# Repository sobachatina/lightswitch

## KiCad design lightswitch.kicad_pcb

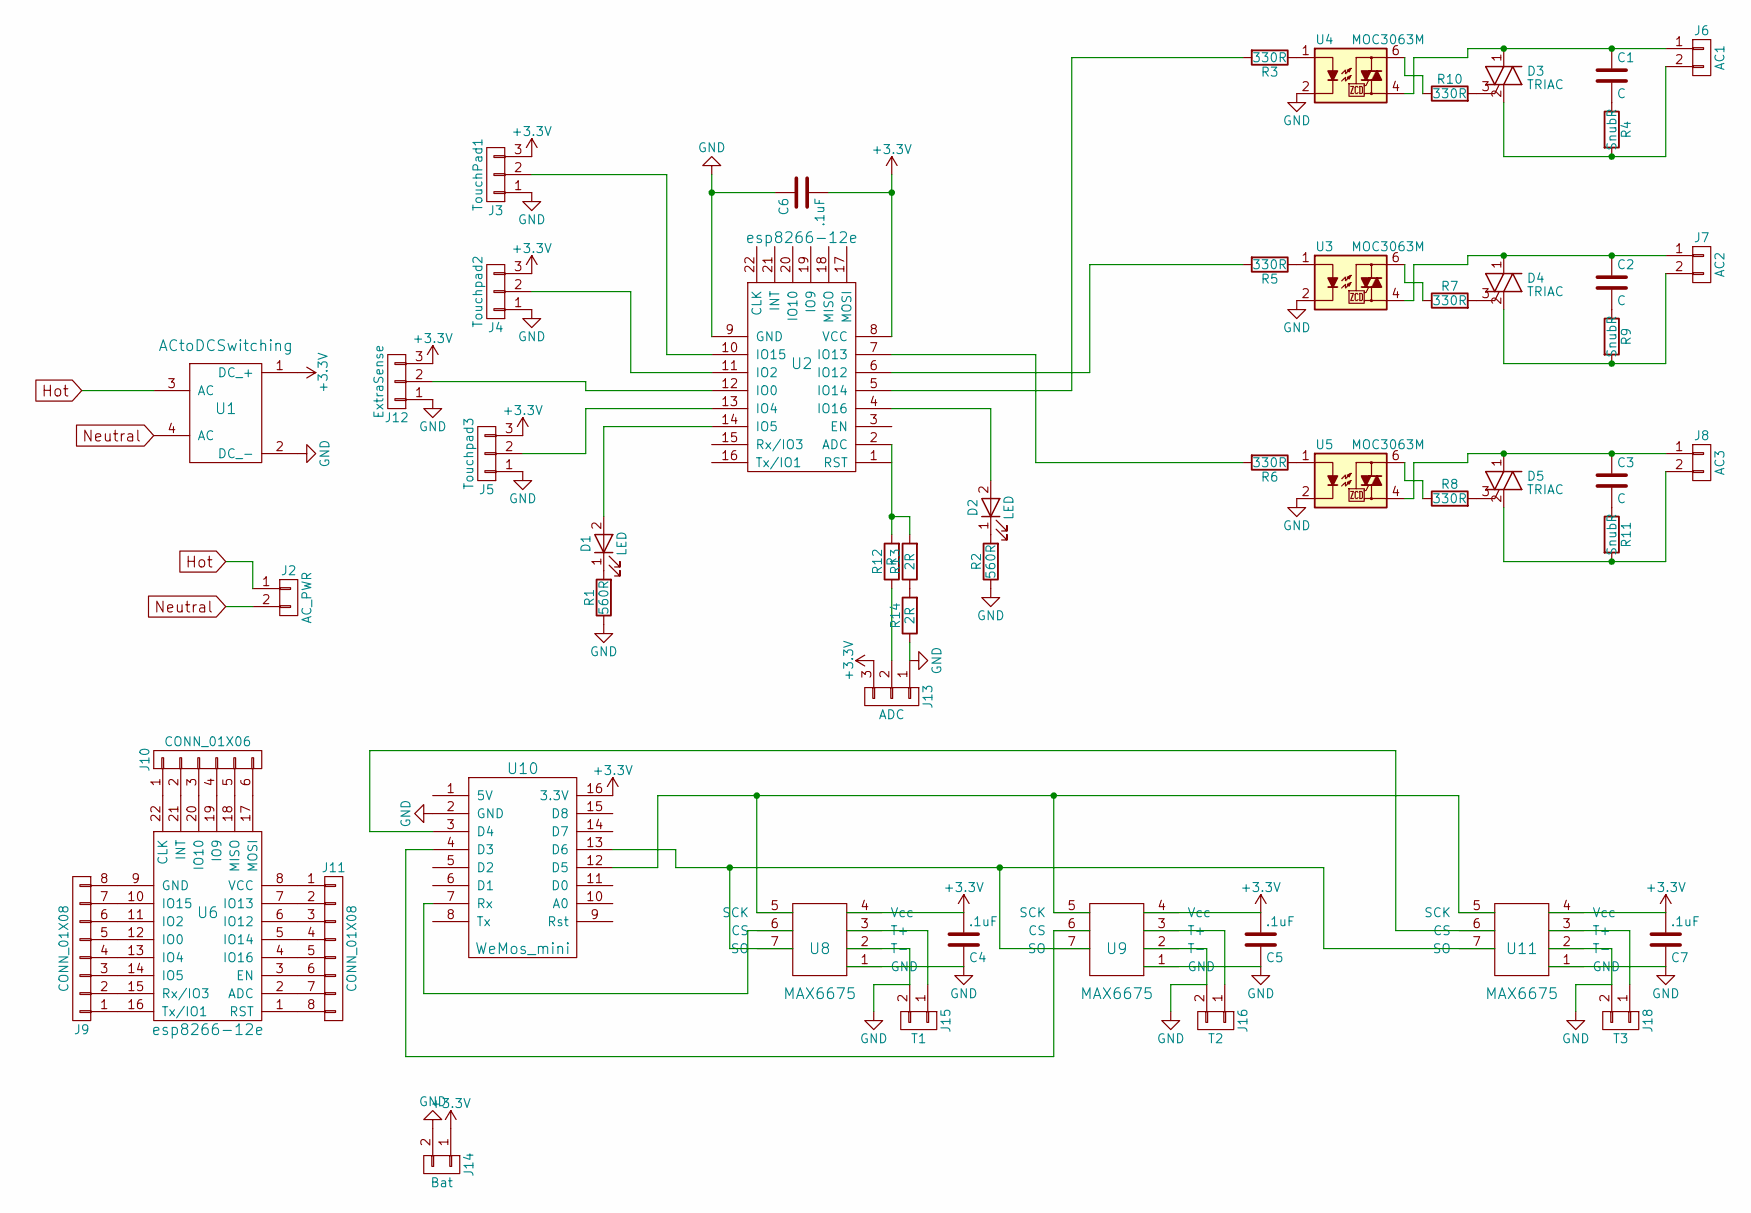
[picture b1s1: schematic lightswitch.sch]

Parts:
C1, C2, C3: C; C_0805_HandSoldering
C4, C5, C6, C7: .1uF; C_0805_HandSoldering
D1, D2: LED; LED_0805_HandSoldering
D3, D4, D5: TRIAC; TO-263-2
J2: AC_PWR; ScrewTerminalBlock2Pin10mm
J3: TouchPad1; Pin_Header_Straight_1x03_Pitch2.54mm
J4: Touchpad2; Pin_Header_Straight_1x03_Pitch2.54mm
J5: Touchpad3; Pin_Header_Straight_1x03_Pitch2.54mm
J6: AC1; ScrewTerminalBlock2Pin10mm
J7: AC2; ScrewTerminalBlock2Pin10mm
J8: AC3; ScrewTerminalBlock2Pin10mm
J9, J11: CONN_01X08; Pin_Header_Straight_1x08_Pitch2.54mm
J10: CONN_01X06; Pin_Header_Straight_1x06_Pitch2.54mm
J12: ExtraSense; Pin_Header_Straight_1x03_Pitch2.54mm
J13: ADC; Pin_Header_Straight_1x03_Pitch2.54mm
J14: Bat; Pin_Header_Straight_1x02_Pitch2.54mm
J15: T1; Pin_Header_Straight_1x02_Pitch2.54mm
J16: T2; Pin_Header_Straight_1x02_Pitch2.54mm
J18: T3; Pin_Header_Straight_1x02_Pitch2.54mm
R1, R2: 560R; R_0805_HandSoldering
R3, R5, R6, R7, R8, R10: 330R; R_0805_HandSoldering
R4, R9, R11: SnubR; R_0805_HandSoldering
R12: R; R_0805_HandSoldering
R13, R14: 2R; R_0805_HandSoldering
U1: ACtoDCSwitching; HLK-PM03
U2: esp8266-12e; ESP-12E_Sides
U3, U4, U5: MOC3063M; DIP-6_W7.62mm
U6: esp8266-12e; ESP-12E
U8, U9, U11: MAX6675; SO-8_5.3x6.2mm_Pitch1.27mm
U10: WeMos_mini; D1_mini_board

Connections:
+3V3: C4.2, C5.2, C6.2, C7.2, J3.3, J4.3, J5.3, J12.3, J13.3, J14.1, U1.1 (DC_+), U2.8 (VCC), U8.4 (Vcc), U9.4 (Vcc), U10.16 (3.3V), U11.4 (Vcc)
GND: C4.1, C5.1, C6.1, C7.1, J3.1, J4.1, J5.1, J12.1, J13.1, J14.2, J15.2, J16.2, J18.2, R1.1, R2.1, R14.1, U1.2 (DC_-), U2.9 (GND), U3.2, U4.2, U5.2, U8.1 (GND), U8.2 (T-), U9.1 (GND), U9.2 (T-), U10.2 (GND), U11.1 (GND), U11.2 (T-)
Hot: J2.1, U1.3 (AC)
unnamed: C1.1, D3.1 (A1), J6.1, U4.4
unnamed: C1.2, R4.1
unnamed: C2.1, D4.1 (A1), J7.1, U3.4
unnamed: C2.2, R9.1
unnamed: C3.1, D5.1 (A1), J8.1, U5.4
unnamed: C3.2, R11.1
unnamed: D1.1 (K), R1.2
unnamed: D1.2 (A), U2.14 (IO5)
unnamed: D2.1 (K), R2.2
unnamed: D2.2 (A), U2.4 (IO16)
unnamed: D3.2 (A2), J6.2, R4.2
unnamed: D3.3 (G), R10.2
unnamed: D4.2 (A2), J7.2, R9.2
unnamed: D4.3 (G), R7.2
unnamed: D5.2 (A2), J8.2, R11.2
unnamed: D5.3 (G), R8.2
unnamed: J3.2, U2.10 (IO15)
unnamed: J4.2, U2.11 (IO2)
unnamed: J5.2, U2.13 (IO4)
unnamed: J9.1, U6.16 (Tx/IO1)
unnamed: J9.2, U6.15 (Rx/IO3)
unnamed: J9.3, U6.14 (IO5)
unnamed: J9.4, U6.13 (IO4)
unnamed: J9.5, U6.12 (IO0)
unnamed: J9.6, U6.11 (IO2)
unnamed: J9.7, U6.10 (IO15)
unnamed: J9.8, U6.9 (GND)
unnamed: J10.1, U6.22 (CLK)
unnamed: J10.2, U6.21 (INT)
unnamed: J10.3, U6.20 (IO10)
unnamed: J10.4, U6.19 (IO9)
unnamed: J10.5, U6.18 (MISO)
unnamed: J10.6, U6.17 (MOSI)
unnamed: J11.1, U6.8 (VCC)
unnamed: J11.2, U6.7 (IO13)
unnamed: J11.3, U6.6 (IO12)
unnamed: J11.4, U6.5 (IO14)
unnamed: J11.5, U6.4 (IO16)
unnamed: J11.6, U6.3 (EN)
unnamed: J11.7, U6.2 (ADC)
unnamed: J11.8, U6.1 (RST)
unnamed: J12.2, U2.12 (IO0)
unnamed: J13.2, R12.1
unnamed: J15.1, U8.3 (T+)
unnamed: J16.1, U9.3 (T+)
unnamed: J18.1, U11.3 (T+)
unnamed: R3.1, U4.1
unnamed: R3.2, U2.5 (IO14)
unnamed: R5.1, U3.1
unnamed: R5.2, U2.6 (IO12)
unnamed: R6.1, U5.1
unnamed: R6.2, U2.7 (IO13)
unnamed: R7.1, U3.6
unnamed: R8.1, U5.6
unnamed: R10.1, U4.6
unnamed: R12.2, R13.2, U2.2 (ADC)
unnamed: R13.1, R14.2
unnamed: U10.3 (D4), U11.6 (CS)
unnamed: U9.6 (CS), U10.4 (D3)
unnamed: U8.6 (CS), U10.7 (Rx)
unnamed: U8.5 (SCK), U9.5 (SCK), U10.12 (D5), U11.5 (SCK)
unnamed: U8.7 (SO), U9.7 (SO), U10.13 (D6), U11.7 (SO)
Neutral: J2.2, U1.4 (AC)

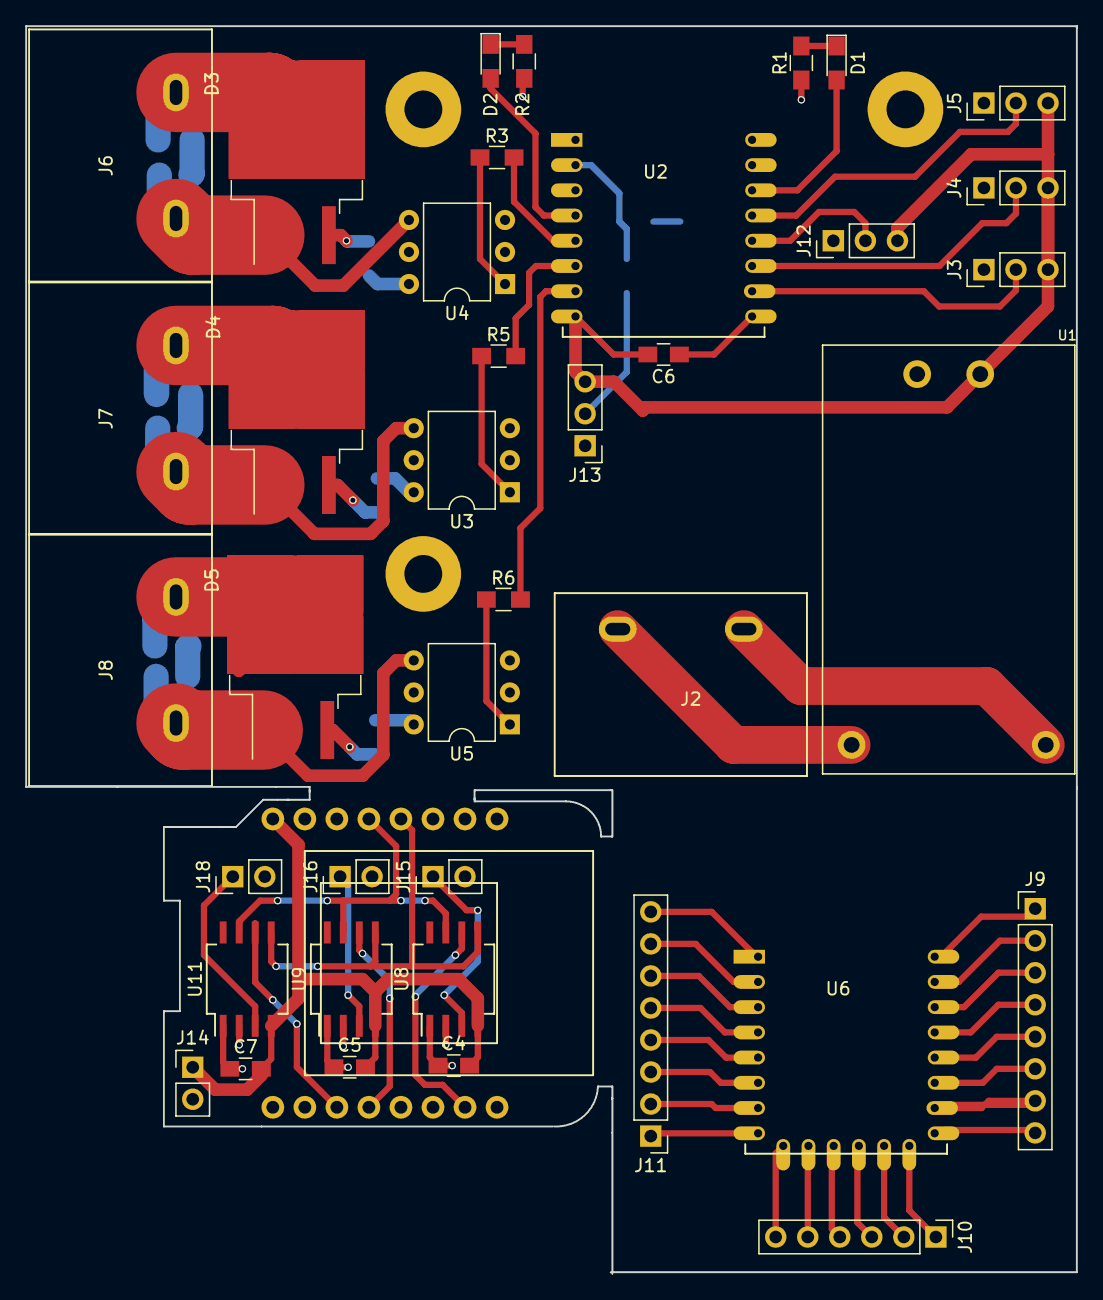
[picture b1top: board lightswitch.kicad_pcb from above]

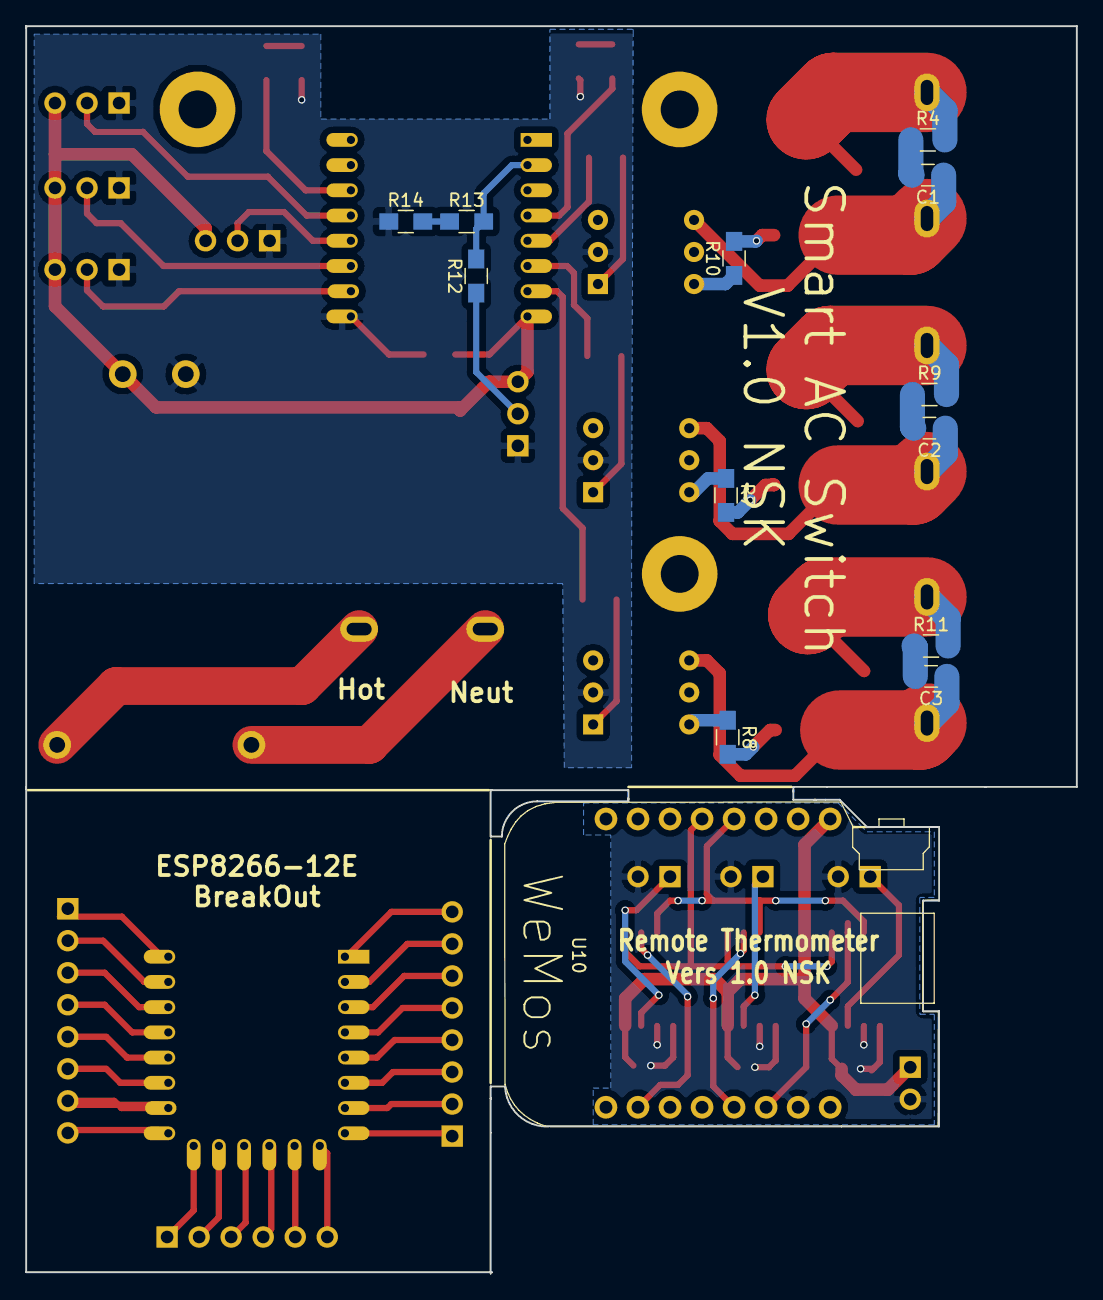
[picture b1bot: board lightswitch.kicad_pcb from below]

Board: 2 copper layers, 83.3 x 98.9 mm, 52 parts (13 on the bottom side), 66 nets.
